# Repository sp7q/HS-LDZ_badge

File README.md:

# HS-LDZ_badge
Hakierspejs Łódź badge, on which we teach people how to solder.

### Assumptions:

- Simple circuit
- Small number of components
- Relatively short assembly time
- Practical use

  The circuit is an implementation of the LM3909 using discrete components, based on the design from the link below :
  
  (https://www.righto.com/2021/01/reverse-engineering-low-power-led.html)

  LTspice model is based on work from link :
  
  (https://softsolder.com/2020/09/03/discrete-transistor-lm3909-led-flasher/)

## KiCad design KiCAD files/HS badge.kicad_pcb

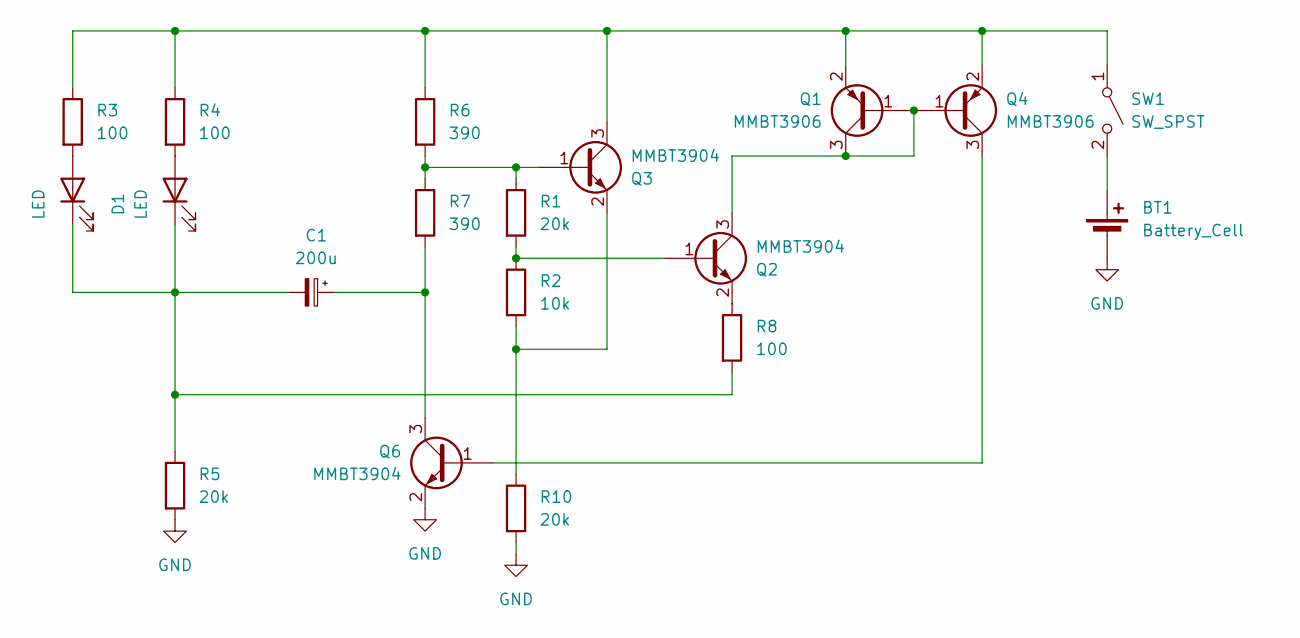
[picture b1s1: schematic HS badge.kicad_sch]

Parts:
BT1: Battery_Cell; BatteryHolder_Keystone_3002_1x2032
C1: 200u; CP_Elec_8x10.5
D1, D2: LED; LED_D5.0mm
Q1, Q4: MMBT3906; TSOT-23_HandSoldering
Q2, Q3, Q6: MMBT3904; TSOT-23_HandSoldering
R1, R5, R10: 20k; R_1206_3216Metric_Pad1.30x1.75mm_HandSolder
R2: 10k; R_1206_3216Metric_Pad1.30x1.75mm_HandSolder
R3, R4, R8: 100; R_1206_3216Metric_Pad1.30x1.75mm_HandSolder
R6, R7: 390; R_1206_3216Metric_Pad1.30x1.75mm_HandSolder
SW1: SW_SPST; SW_SPDT_CK-JS102011SAQN

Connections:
GND: BT1.2 (-), Q6.2 (E), R5.2, R10.2
unnamed: BT1.1 (+), SW1.2 (B)
unnamed: D1.2 (A), R4.2
unnamed: C1.2, D1.1 (K), D2.1 (K), R5.1, R8.2
unnamed: D2.2 (A), R3.2
unnamed: Q1.1 (B), Q1.3 (C), Q2.3 (C), Q4.1 (B)
unnamed: Q1.2 (E), Q3.3 (C), Q4.2 (E), R3.1, R4.1, R6.1, SW1.1 (A)
unnamed: Q2.1 (B), R1.2, R2.1
unnamed: Q2.2 (E), R8.1
unnamed: Q3.1 (B), R1.1, R6.2, R7.1
unnamed: Q3.2 (E), R2.2, R10.1
unnamed: Q4.3 (C), Q6.1 (B)
unnamed: C1.1, Q6.3 (C), R7.2

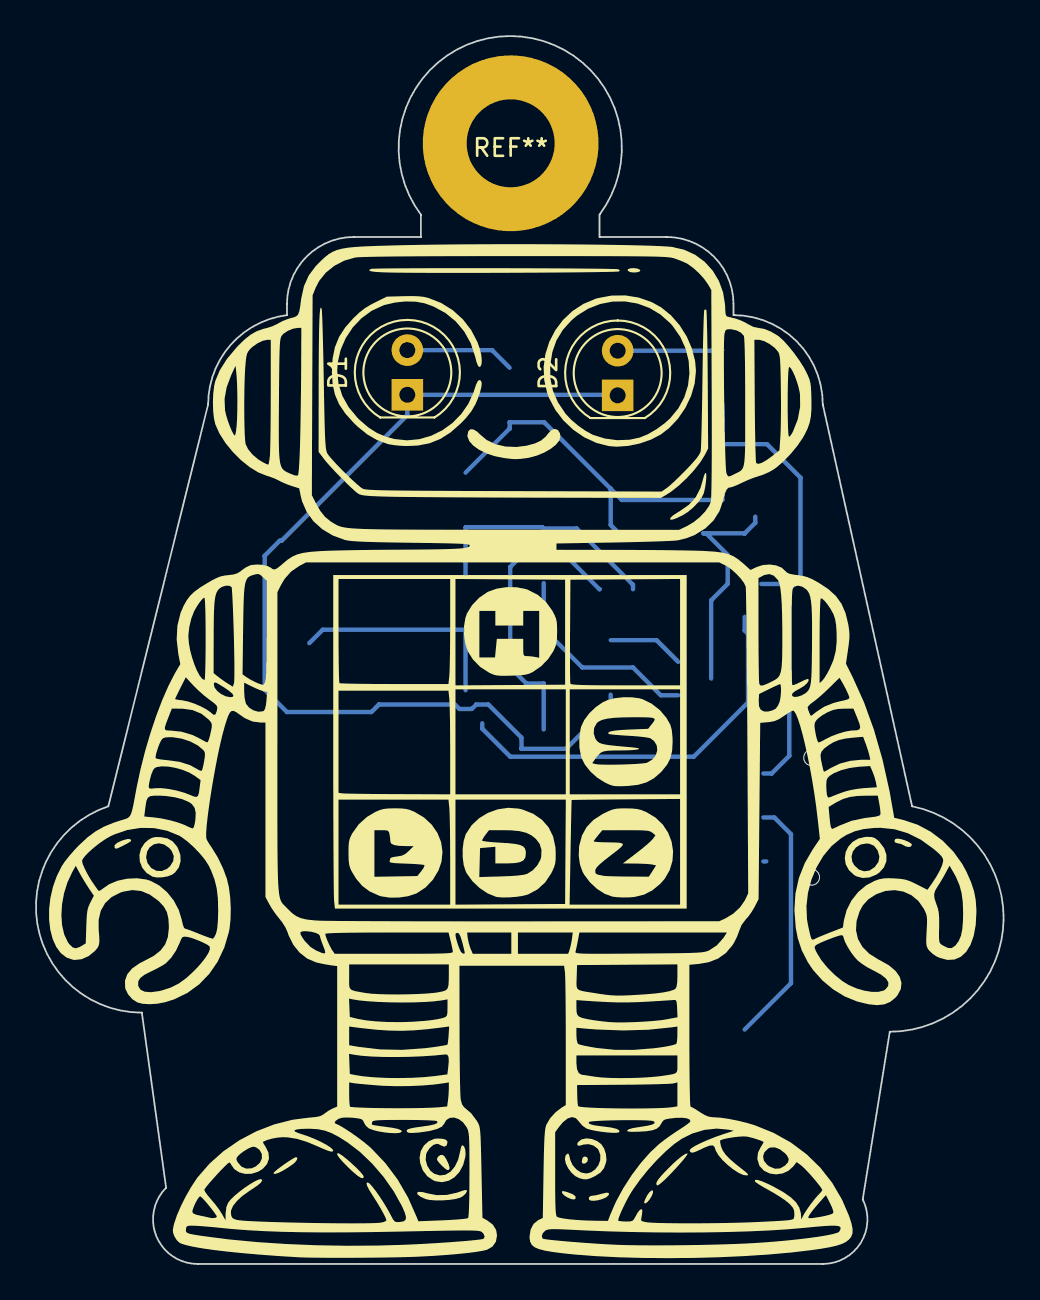
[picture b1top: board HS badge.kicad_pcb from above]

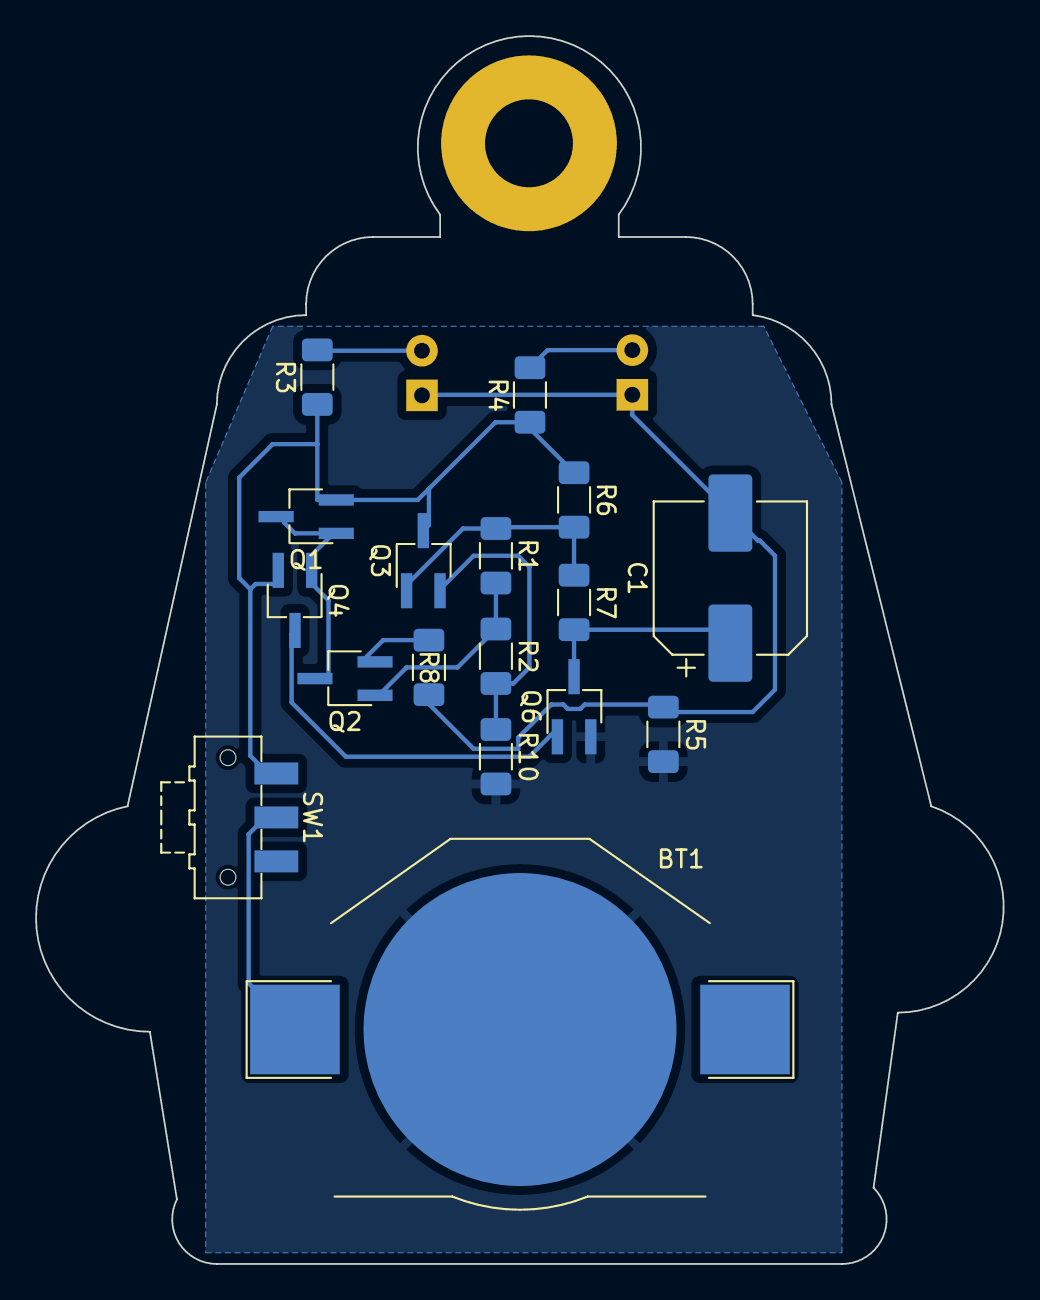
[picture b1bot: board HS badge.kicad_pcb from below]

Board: 2 copper layers, 55.0 x 69.8 mm, 19 parts (17 on the bottom side), 13 nets.

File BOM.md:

### Component List

| LP | Symbol   | Link                                                                                          | Quantity |
|----|----------|-----------------------------------------------------------------------------------------------|----------|
| 1  | MMBT3906 | [MMBT3906](https://www.tme.eu/pl/details/mmbt3906-dio/tranzystory-pnp-s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 | 2        |
| 2  | MMBT3904 | [MMBT3904](https://www.tme.eu/pl/details/mmbt3904-dio/tranzystory-npn-s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 | 3        |
| 3  | LED      | [LED](https://www.tme.eu/pl/details/383-2sdrc_s530-a3/diody-led-th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       | 2        |
| 4  | Capacitor| [Capacitor](https://www.tme.eu/pl/details/ucd0j471mnl1gs/kondensatory-el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       | 1        |
| 5  | 390      | [390](https://www.tme.eu/pl/details/smd1206-390r-1%25/rezystory-sm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 | 2        |
| 6  | 100      | [100](https://www.tme.eu/pl/details/mr12x1000ftl/rezystory-smd/walsin/)                        | 3        |
| 7  | 10k      | [10k](https://www.tme.eu/pl/details/ac1206fr-0710kl/rezystory-smd/yageo/)                      | 1        |
| 8  | 20k      | [20k](https://www.tme.eu/pl/details/crcw120620k0fktabc/rezystory-s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                  | 3        |
| 9  | CR2032   |                                                                                               | 1        |
| 10 | Battery holder KEY3002 | [Koszyk KEY3002](https://www.tme.eu/pl/details/keys3002/baterie-pojemniki-i-u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 | 1        |
| 11 | Switch   | [Switch](https://www.tme.eu/pl/details/js102011saqn/przelaczniki-suwa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                | 1        |
| 12 | PCB      |                                                                                               | 1        |
